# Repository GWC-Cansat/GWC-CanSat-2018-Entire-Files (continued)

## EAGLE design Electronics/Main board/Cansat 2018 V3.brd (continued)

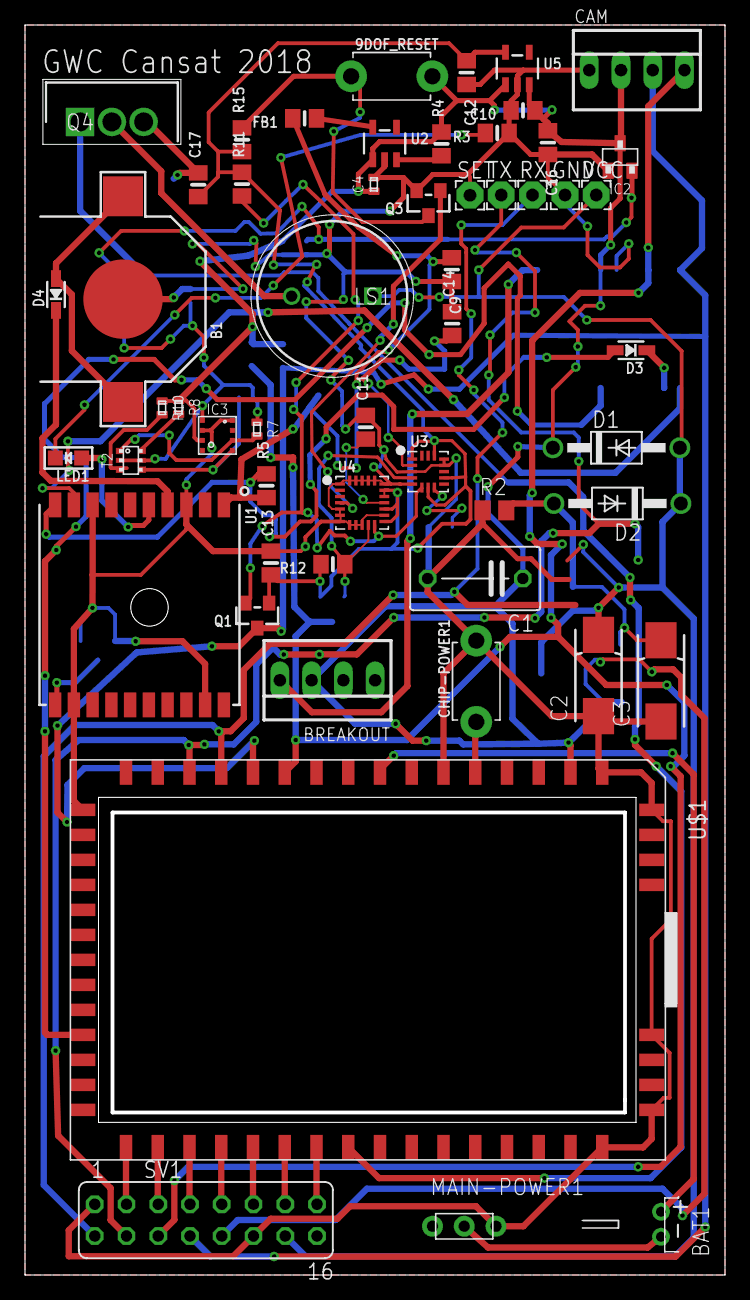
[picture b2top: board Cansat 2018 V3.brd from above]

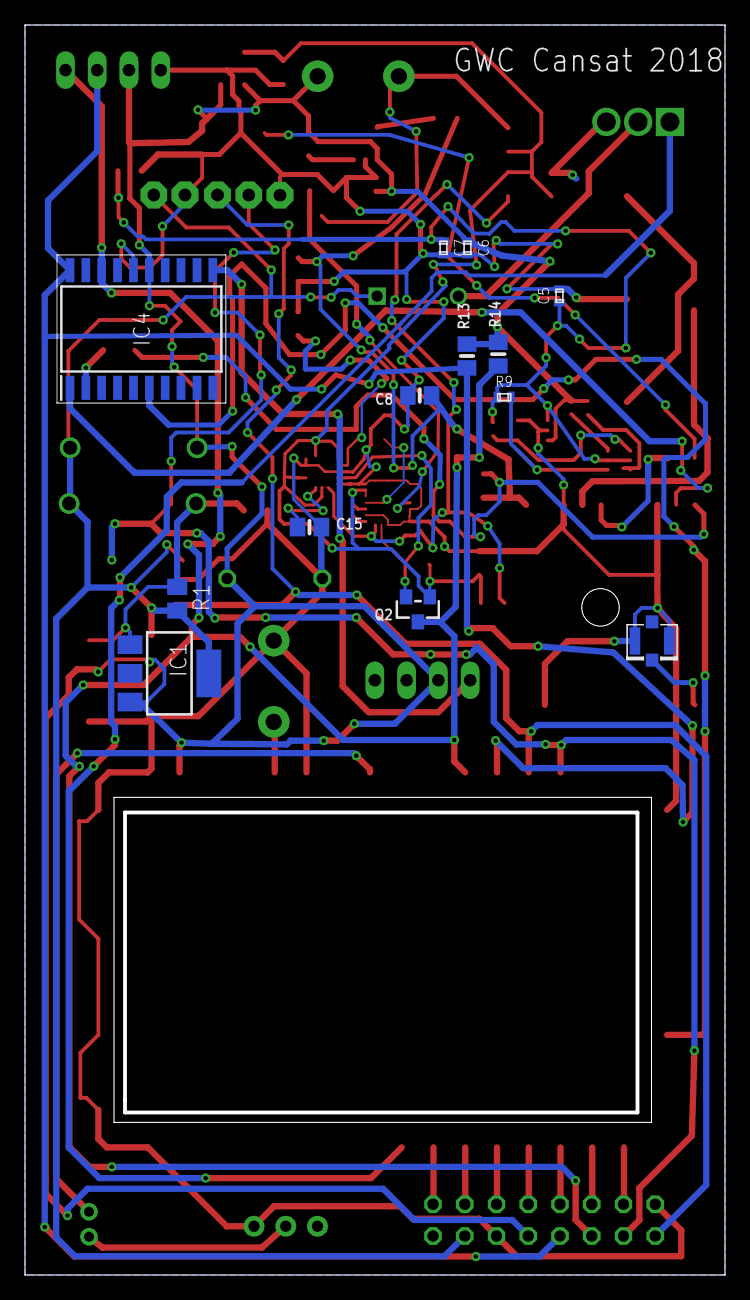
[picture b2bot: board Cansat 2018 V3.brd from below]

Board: 2 copper layers, 56.0 x 100.0 mm, 67 parts (13 on the bottom side), 46 nets.

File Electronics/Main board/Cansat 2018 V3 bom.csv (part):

"Part";"Value";"Device";"Package";"Description";"3D_PACKAGE";"ALLIED_NUMBER";"DESCRIPTION";"HEIGHT";"MANUFACTURER_NAME";"MANUFACTURER_PART_NUMBER";"MF";"MPN";"OC_FARNELL";"OC_NEWARK";"OTHER_PART_NUMBER";"PARTNUMBER";"RS_PART_NUMBER";"SUPPLIER_NAME";
"9DOF_RESET";"";"SWITCH_PUSHBUTTONEVQ-PE";"TACT_PANA-EVQ";"Buttons";"";"";"";"";"";"";"";"";"";"";"";"";"";"";
"B1";"CR1220";"BATTERYCR1220_SMT";"CR1220";"CR1220 SMT - Digikey: 3001K-ND";"";"";"";"";"";"";"";"";"";"";"";"";"";"";
"BAT1";"3.7V";"JST_2PIN-THM-RA";"JST-PH-2-THM-RA";"JST 2-Pin Connectors of various flavors";"";"";"";"";"";"";"";"";"";"";"";"";"";"";
"BREAKOUT";"22-23-2041";"22-23-2041";"22-23-2041";".100" (2.54mm) Center Header - 4 Pin";"";"";"";"";"";"";"MOLEX";"22-23-2041";"1462920";"38C0355";"";"";"";"";
"C1";"0.1uF";"C-EU075-052X106";"C075-052X106";"CAPACITOR, European symbol";"";"";"";"";"";"";"";"";"";"";"";"";"";"";
"C2";"1uF";"CPOL-US085CS-1AR";"085CS_1AR";"POLARIZED CAPACITOR, American symbol";"";"";"";"";"";"";"";"";"";"";"";"";"";"";
"C3";"10uF";"CPOL-US085CS-1AR";"085CS_1AR";"POLARIZED CAPACITOR, American symbol";"";"";"";"";"";"";"";"";"";"";"";"";"";"";
"C4";"100n";"CAPACITOR-0402";"C0402";"Capacitors";"";"";"";"";"";"";"";"";"";"";"";"";"";"";
"C5";"100n";"CAPACITOR-0402";"C0402";"Capacitors";"";"";"";"";"";"";"";"";"";"";"";"";"";"";
"C6";"2u2";"CAPACITOR-0402";"C0402";"Capacitors";"";"";"";"";"";"";"";"";"";"";"";"";"";"";
"C7";"2u2";"CAPACITOR-0402";"C0402";"Capacitors";"";"";"";"";"";"";"";"";"";"";"";"";"";"";
"C8";"0.1uF";"CAP_CERAMIC0805-NOOUTLINE";"0805-NO";"Ceramic Capacitors";"";"";"";"";"";"";"";"";"";"";"";"";"";"";
"C9";"10uF";"CAP_CERAMIC0805-NOOUTLINE";"0805-NO";"Ceramic Capacitors";"";"";"";"";"";"";"";"";"";"";"";"";"";"";
"C10";"10uF";"CAP_CERAMIC0805-NOOUTLINE";"0805-NO";"Ceramic Capacitors";"";"";"";"";"";"";"";"";"";"";"";"";"";"";
"C11";"0.1uF";"CAP_CERAMIC0805-NOOUTLINE";"0805-NO";"Ceramic Capacitors";"";"";"";"";"";"";"";"";"";"";"";"";"";"";
"C12";"0.1uF";"CAP_CERAMIC0805-NOOUTLINE";"0805-NO";"Ceramic Capacitors";"";"";"";"";"";"";"";"";"";"";"";"";"";"";
"C13";"10uF";"CAP_CERAMIC0805-NOOUTLINE";"0805-NO";"Ceramic Capacitors";"";"";"";"";"";"";"";"";"";"";"";"";"";"";
"C14";"0.1uF";"CAP_CERAMIC0805-NOOUTLINE";"0805-NO";"Ceramic Capacitors";"";"";"";"";"";"";"";"";"";"";"";"";"";"";
"C15";"0.1uF";"CAP_CERAMIC0805-NOOUTLINE";"0805-NO";"Ceramic Capacitors";"";"";"";"";"";"";"";"";"";"";"";"";"";"";
"C16";"10µF";"CAP_CERAMIC0805-NOOUTLINE";"0805-NO";"Ceramic Capacitors";"";"";"";"";"";"";"";"";"";"";"";"";"";"";
"C17";"10µF";"CAP_CERAMIC0805-NOOUTLINE";"0805-NO";"Ceramic Capacitors";"";"";"";"";"";"";"";"";"";"";"";"";"";"";
"CAM";"22-23-2041";"22-23-2041";"22-23-2041";".100" (2.54mm) Center Header - 4 Pin";"";"";"";"";"";"";"MOLEX";"22-23-2041";"1462920";"38C0355";"";"";"";"";
"CHIP-POWER1";"";"SWITCH_PUSHBUTTONEVQ-PE";"TACT_PANA-EVQ";"Buttons";"";"";"";"";"";"";"";"";"";"";"";"";"";"";
"D1";"1N4002";"1N4004";"DO41-10";"DIODE";"";"";"";"";"";"";"";"";"";"";"";"";"";"";
"D2";"1N4002";"1N4004";"DO41-10";"DIODE";"";"";"";"";"";"";"";"";"";"";"";"";"";"";
"D3";"1N4148";"DIODESOD-323";"SOD-323";"Diode";"";"";"";"";"";"";"";"";"";"";"";"";"";"";
"D4";"CUS520";"DIODESOD-323";"SOD-323";"Diode";"";"";"";"";"";"";"";"";"";"";"";"";"";"";
"FB1";"Ferrite";"FERRITE-0805NO";"0805-NO";"Ferrite Bead";"";"";"";"";"";"";"";"";"";"";"";"";"";"";
"GND";"";"2,15/1,0";"2,15/1,0";"THROUGH-HOLE PAD";"";"";"";"";"";"";"";"";"";"";"";"";"";"";
"IC1";"LM317MBSTT3";"LM317MBSTT3";"SOT223";"500 mA Adjustable Output Positive Voltage Regulator";"";"";"";"";"";"";"";"";"";"";"";"LM317M";"";"";
"IC2";"LDO-TS9011-3V3";"LDO-TS9011-3V3";"SOT23";"LDOs";"";"";"";"";"";"";"";"";"";"";"";"";"";"";
"IC3";"BME680";"BME680";"BME680";"Bosch BME280 Humidity, Pressure, Air Quality Sensor";"";"";"";"";"";"";"";"";"";"";"";"";"";"";
"IC4";"ATTINY167-SU";"ATTINY167-SU";"SOIC127P1032X265-20N";"Atmel ATTINY167-SU, 8bit AVR Microcontroller, 20MHz, 16 kB Flash, 20-Pin SOIC";"";"";"Atmel ATTINY167-SU, 8bit AVR Microcontroller, 20MHz, 16 kB Flash, 20-Pin SOIC";"2.65mm";"Microchip";"ATTINY167-SU";"";"";"";"";"";"";"1330967";"RS";
"LED1";"RED";"LED0805";"CHIPLED_0805";"LED";"";"";"";"";"";"";"";"";"";"";"";"";"";"";
"LS1";"3030161";"3030161";"CAPPRD650W70D1200H950";"RS Pro 8V Magnetic Buzzer, 92dB Continuous";"";"";"RS Pro 8V Magnetic Buzzer, 92dB Continuous";"9.5mm";"RS Components";"3030161";"";"";"";"";"";"";"3030161";"RS";
"MAIN-POWER1";"";"EG1218S";"EG1218";"SLIDING SWITCH";"";"";"";"";"";"";"";"";"";"";"";"";"";"";
"Q1";"BSS138";"MOSFET-NWIDE";"SOT23-WIDE";"N-Channel Mosfet";"";"";"";"";"";"";"";"";"";"";"";"";"";"";
"Q2";"BSS138";"MOSFET-NWIDE";"SOT23-WIDE";"N-Channel Mosfet";"";"";"";"";"";"";"";"";"";"";"";"";"";"";
"Q3";"BSS138";"MOSFET-NWIDE";"SOT23-WIDE";"N-Channel Mosfet";"";"";"";"";"";"";"";"";"";"";"";"";"";"";
"Q4";"IRLZ34NPBF";"IRLZ34NPBF";"TO254P469X1042X1967-3P";"N-channel MOSFET,IRLZ34N 30A 55V";"";"70017120";"N-channel MOSFET,IRLZ34N 30A 55V";"4.69mm";"International Rectifier";"IRLZ34NPBF";"";"";"";"";"";"";"2509061391";"RS";
"R1";"240O";"R-US_M0805";"M0805";"RESISTOR, American symbol";"";"";"";"";"";"";"";"";"";"";"";"";"";"";
"R2";"720O";"R-US_M0805";"M0805";"RESISTOR, American symbol";"";"";"";"";"";"";"";"";"";"";"";"";"";"";
"R3";"1K";"RESISTOR0805_NOOUTLINE";"0805-NO";"Resistors";"";"";"";"";"";"";"";"";"";"";"";"";"";"";
"R4";"10K";"RESISTOR0805_NOOUTLINE";"0805-NO";"Resistors";"";"";"";"";"";"";"";"";"";"";"";"";"";"";
"R5";"10K";"RESISTOR0805_NOOUTLINE";"0805-NO";"Resistors";"";"";"";"";"";"";"";"";"";"";"";"";"";"";
"R7";"4k7";"RESISTOR-0402";"C0402";"Resistors";"";"";"";"";"";"";"";"";"";"";"";"";"";"";
"R8";"4k7";"RESISTOR-0402";"C0402";"Resistors";"";"";"";"";"";"";"";"";"";"";"";"";"";"";
"R9";"4k7";"RESISTOR-0402";"C0402";"Resistors";"";"";"";"";"";"";"";"";"";"";"";"";"";"";
"R10";"4k7";"RESISTOR-0402";"C0402";"Resistors";"";"";"";"";"";"";"";"";"";"";"";"";"";"";
"R11";"10K";"RESISTOR0805_NOOUTLINE";"0805-NO";"Resistors";"";"";"";"";"";"";"";"";"";"";"";"";"";"";
"R12";"10K";"RESISTOR0805_NOOUTLINE";"0805-NO";"Resistors";"";"";"";"";"";"";"";"";"";"";"";"";"";"";
"R13";"10K";"RESISTOR0805_NOOUTLINE";"0805-NO";"Resistors";"";"";"";"";"";"";"";"";"";"";"";"";"";"";
"R14";"10K";"RESISTOR0805_NOOUTLINE";"0805-NO";"Resistors";"";"";"";"";"";"";"";"";"";"";"";"";"";"";
"R15";"10K";"RESISTOR0805_NOOUTLINE";"0805-NO";"Resistors";"";"";"";"";"";"";"";"";"";"";"";"";"";"";
"RX";"";"2,15/1,0";"2,15/1,0";"THROUGH-HOLE PAD";"";"";"";"";"";"";"";"";"";"";"";"";"";"";
"SET";"";"2,15/1,0";"2,15/1,0";"THROUGH-HOLE PAD";"";"";"";"";"";"";"";"";"";"";"";"";"";"";
"SV1";"";"FE08-2";"FE08-2";"FEMALE HEADER";"";"";"";"";"";"";"";"";"unknown";"unknown";"";"";"";"";
"T2";"BSS138PS";"BSS138PS";"SOT363";"BSS138 Dual N-Channel MOSFET (UGS +/-20V, RDS 1Ohm, ID 320mA)";"";"";"";"";"";"";"";"";"";"";"";"";"";"";
"TX";"";"2,15/1,0";"2,15/1,0";"THROUGH-HOLE PAD";"";"";"";"";"";"";"";"";"";"";"";"";"";"";
"U$1";"CHIP_PRO";"CHIP_PRO";"CHIP_PRO";"";"";"";"";"";"";"";"";"";"";"";"";"";"";"";
"U$20";"U.FL";"U.FL";"U.FL";"U.FL Antenna Connector";"";"";"";"";"";"";"";"";"";"";"";"";"";"";
"U1";"FGPMMOPA6H";"GPS_FGPMMOPA6H";"FGPMMOPA6H";"GPS Module - MTK MT3339 Chipset, -165dBm sensitivity, 22 channels, 10Hz, auto-select external antenna options";"";"";"";"";"";"";"";"";"";"";"";"";"";"";
"U2";"MIC5225-3.3";"VREG_SOT23-5";"SOT23-5";"SOT23-5 Fixed Voltage Regulators";"";"";"";"";"";"";"";"";"";"";"";"";"";"";
"U3";"FXOS8700CQ";"ACCEL_MAG_FXOS8700CQ";"QFN16_3MM_FREESCALE_5X3";"FX0S8700CQ - 3-Axis Accelerometer and Magnetometer";"";"";"";"";"";"";"";"";"";"";"";"";"";"";
"U4";"FXAS21002C";"GYRO_FXAS21002C";"QFN24_4MM_FREESCALE_7X5";"FXAS21002C - 3 Axis Gyroscope - 250/500/1000/2000dps";"";"";"";"";"";"";"";"";"";"";"";"";"";"";
"U5";"MIC5225-3.3V";"VREG_SOT23-5";"SOT23-5";"SOT23-5 Fixed Voltage Regulators";"";"";"";"";"";"";"";"";"";"";"";"";"";"";
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
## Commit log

2018-04-16 GWC Cansat 2018 post-campaign update 1
    These are the latest versions of scripts from the campaign, although they are still fairly outdated and will likely not work. The final schematics and board designs for our electronics are also attac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
